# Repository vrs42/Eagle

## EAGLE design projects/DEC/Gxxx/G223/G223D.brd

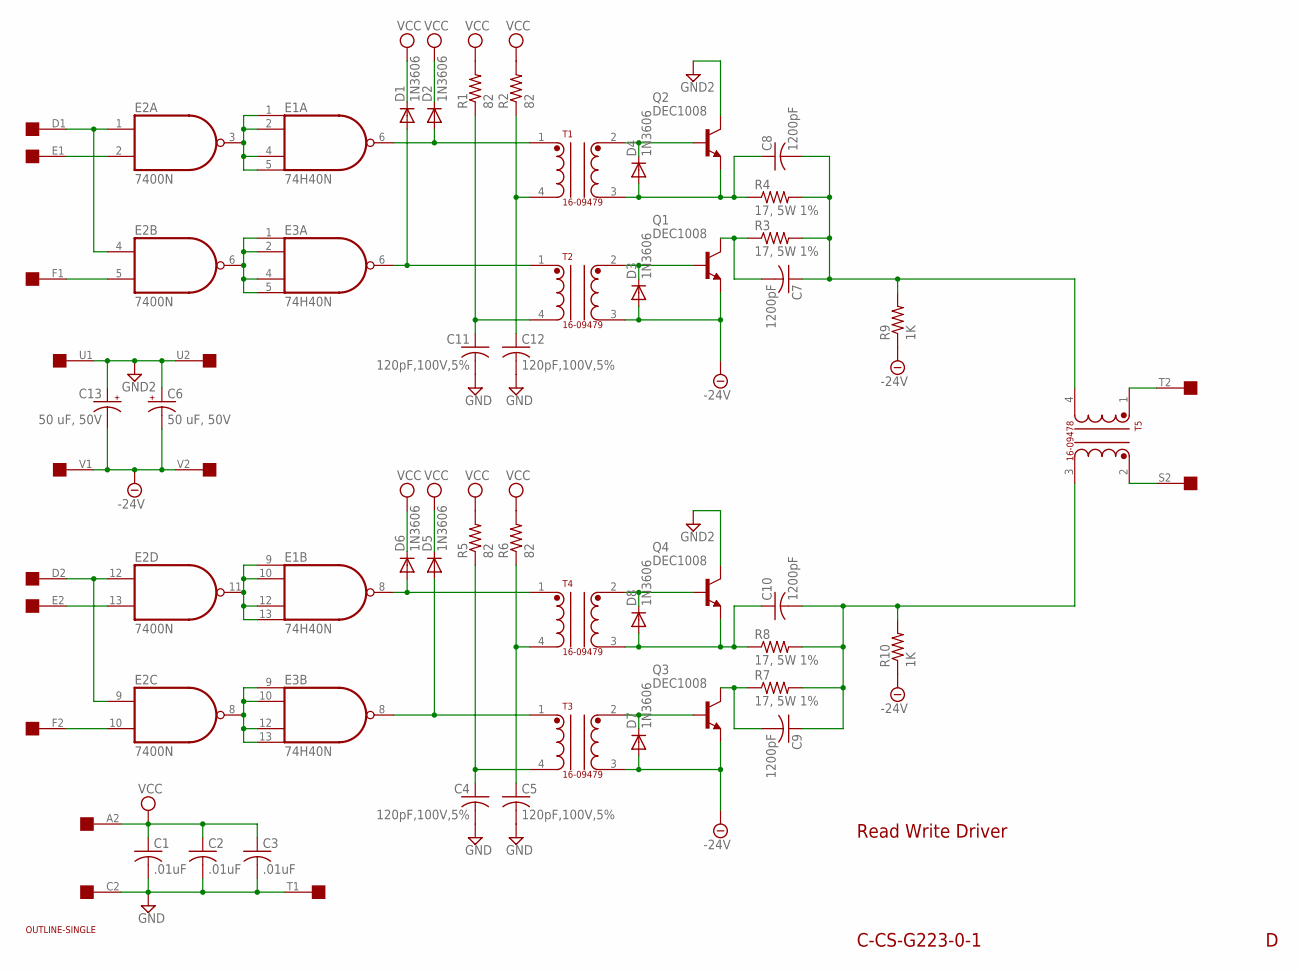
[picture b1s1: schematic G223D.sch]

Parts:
C1, C2, C3: .01uF; C050-025X075
C4, C5, C11, C12: 120pF,100V,5%; C075-032X103
C6, C13: 50 uF, 50V; E30-10
C7, C8, C9, C10: 1200pF; C075-032X103
D1, D2, D3, D4, D5, D6, D7, D8: 1N3606; DO35-10
E1, E3: 74H40N; DIL14
E2: 7400N; DIL14
EDGE1: EDGE-2CONNECTOR; EDGE-CON2
Q1, Q2, Q3, Q4: DEC1008; TO5
R1, R2, R5, R6: 82; 0207/10
R3, R4, R7, R8: 17, 5W 1%; VTA52
R9, R10: 1K; 0207/10
T1, T2, T3, T4: 16-09479; TRANSFORMER-SIL4
T5: 16-09478; TRANSFORMER-SIL4
U$1: OUTLINE-SINGLE; SINGLE

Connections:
-24V: C6.-, C13.-, D3.A, D7.A, EDGE1.V1, EDGE1.V2, Q1.1 (E), Q3.1 (E), R9.1, R10.1, T2.3, T3.3
GND: C1.2, C2.2, C3.2, C4.2, C5.2, C11.2, C12.2, E1.7 (GND), E2.7 (GND), E3.7 (GND), EDGE1.C2, EDGE1.T1
GND2: C6.+, C13.+, EDGE1.U1, EDGE1.U2, Q2.3 (C), Q4.3 (C)
unnamed: E1.1 (I0), E1.2 (I1), E1.4 (I2), E1.5 (I3), E2.3 (O)
unnamed: E2.1 (I0), E2.4 (I0), EDGE1.D1
unnamed: E2.2 (I1), EDGE1.E1
unnamed: E1.9 (I0), E1.10 (I1), E1.12 (I2), E1.13 (I3), E2.11 (O)
unnamed: E2.6 (O), E3.1 (I0), E3.2 (I1), E3.4 (I2), E3.5 (I3)
unnamed: E2.8 (O), E3.9 (I0), E3.10 (I1), E3.12 (I2), E3.13 (I3)
unnamed: E2.5 (I1), EDGE1.F1
unnamed: D2.A, E1.6 (O), T1.1
unnamed: D1.A, E3.6 (O), T2.1
unnamed: D6.A, E1.8 (O), T4.1
unnamed: D5.A, E3.8 (O), T3.1
unnamed: E2.9 (I0), E2.12 (I0), EDGE1.D2
unnamed: E2.13 (I1), EDGE1.E2
unnamed: E2.10 (I1), EDGE1.F2
unnamed: EDGE1.S2, T5.2
unnamed: EDGE1.T2, T5.1
unnamed: C7.1, C8.2, R3.2, R4.2, R9.2, T5.4
unnamed: C8.1, D4.A, Q2.1 (E), R4.1, T1.3
unnamed: C7.2, Q1.3 (C), R3.1
unnamed: C9.1, C10.2, R7.2, R8.2, R10.2, T5.3
unnamed: D7.C, Q3.2 (B), T3.2
unnamed: C9.2, Q3.3 (C), R7.1
unnamed: C10.1, D8.A, Q4.1 (E), R8.1, T4.3
unnamed: C11.1, R1.1, T2.4
unnamed: C12.1, R2.1, T1.4
unnamed: C5.1, R6.1, T4.4
unnamed: C4.1, R5.1, T3.4
unnamed: D3.C, Q1.2 (B), T2.2
unnamed: D4.C, Q2.2 (B), T1.2
unnamed: D8.C, Q4.2 (B), T4.2
VCC: C1.1, C2.1, C3.1, D1.C, D2.C, D5.C, D6.C, E1.14 (VCC), E2.14 (VCC), E3.14 (VCC), EDGE1.A2, R1.2, R2.2, R5.2, R6.2

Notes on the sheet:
Read Write Driver
C-CS-G223-0-1

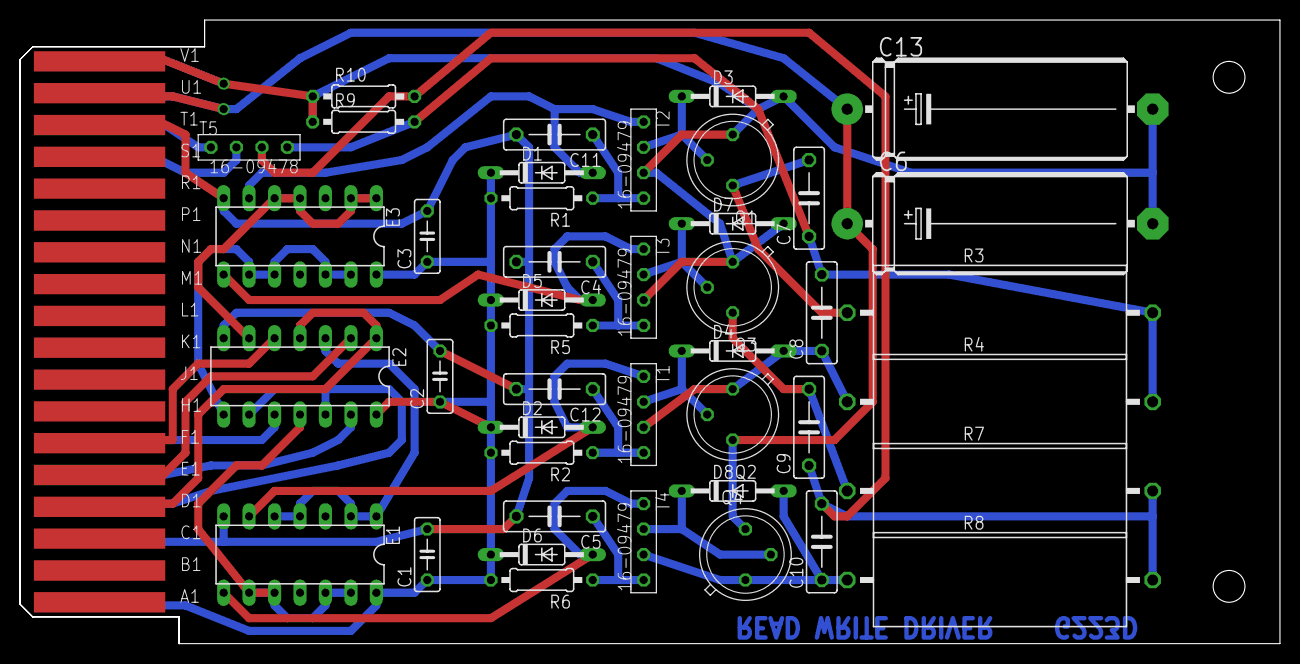
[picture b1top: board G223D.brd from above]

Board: 2 copper layers, 125.7 x 62.2 mm, 45 parts (0 on the bottom side), 34 nets.

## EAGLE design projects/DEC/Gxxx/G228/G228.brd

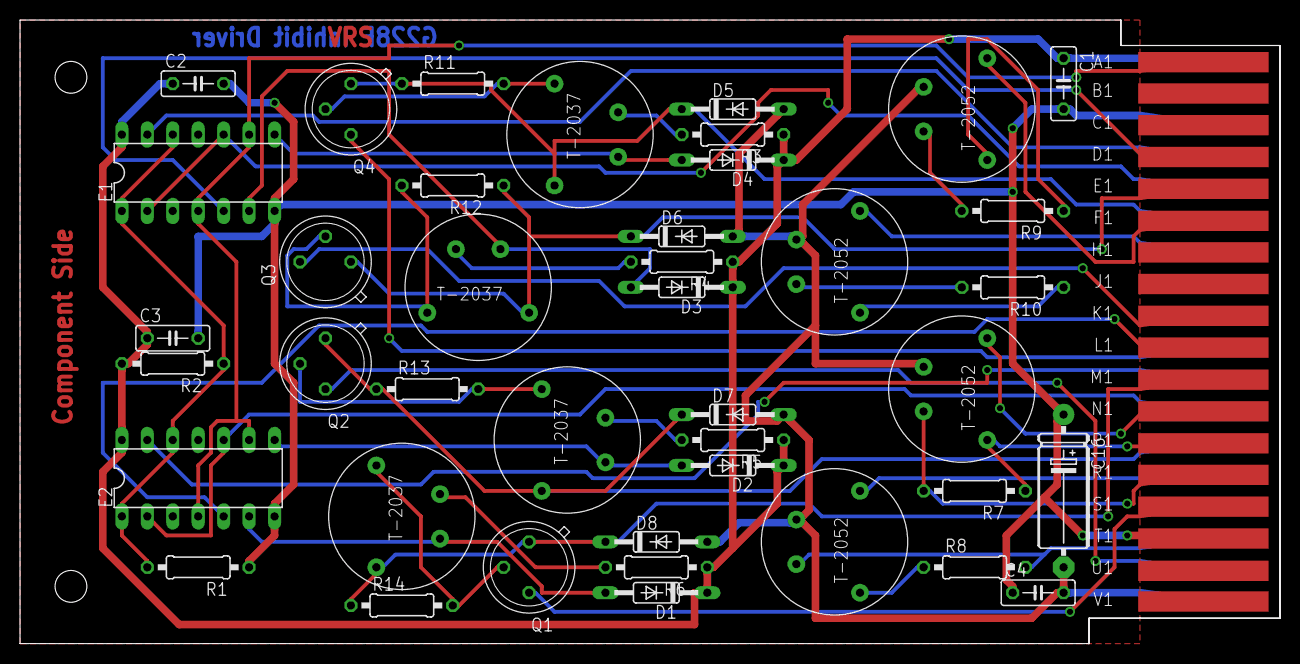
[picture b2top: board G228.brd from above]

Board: 2 copper layers, 125.7 x 62.2 mm, 43 parts (0 on the bottom side), 43 nets.

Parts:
C1, C2, C3, C4: .01uf; C050-025X075
C16: 20uf 50V; E15-5
D1, D2, D3, D4: 1N3606; DO35-10
D5, D6, D7, D8: 1N3653; DO35-10
E1, E2: 7440N; DIL14
Q1, Q2, Q3, Q4: TO39
R1: 750; 0207/10
R2, R3, R4, R5, R6: 330; 0207/10
R7, R8, R9, R10: 270; 0207/10
R11, R12, R13, R14: 470; 0207/10
T1, T2, T3, T4: T-2037; TRANSFORMER
T5, T6, T7, T8: T-2052; TRANSFORMER
U$1: EDGE-CON2
U$2: OUTLINE-SINGLE-R; SINGLE-R

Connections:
-24V: C4.2, C16.-, D5.A, D6.A, D7.A, D8.A, T5.4, T6.4, T7.4, T8.4, U$1.V2
A1: E1.4, E1.9, E2.4, E2.9, U$1.A1
D1: E1.5, U$1.D1
D2: E1.13, U$1.D2
E1: D6.C, Q3.1, R12.1, T3.2, U$1.E1
E2: E1.2, E1.10, U$1.E2
F1: T7.2, U$1.F1
F2: D5.C, Q4.1, R11.1, T4.2, U$1.F2
GND: C1.2, C2.2, C3.2, C4.1, C16.+, E1.7, E2.7, R1.1, U$1.C2, U$1.T1
H1: R9.1, T7.7
H2: T8.2, U$1.H2
J1: R9.2, T7.5
J2: R10.1, T8.7
K1: Q3.3, U$1.K1
K2: R10.2, T8.5
L1: E2.5, U$1.L1
L2: Q4.3, U$1.L2
M1: D8.C, Q1.1, R14.1, T1.2, U$1.M1
M2: E2.13, U$1.M2
N1: T5.2, U$1.N1
N2: E2.2, E2.10, U$1.N2
unnamed: E1.1, E1.12, E2.1, E2.12, R1.2, R2.1
unnamed: D1.A, E2.6, T1.4
unnamed: D2.A, E2.8, T2.4
unnamed: D3.A, E1.6, T3.4
unnamed: D4.A, E1.8, T4.4
unnamed: R6.2, T1.5
unnamed: R5.2, T2.5
unnamed: R4.2, T3.5
unnamed: R3.2, T4.5
unnamed: Q4.2, R11.2, T4.7
unnamed: Q3.2, R12.2, T3.7
unnamed: Q2.2, R13.2, T2.7
unnamed: Q1.2, R14.2, T1.7
P1: R7.1, T5.7, U$1.P1
P2: D7.C, Q2.1, R13.1, T2.2, U$1.P2
R1: R7.2, T5.5, U$1.R1
R2: T6.2, U$1.R2
S1: Q1.3, U$1.S1
S2: R8.1, T6.7
T2: R8.2, T6.5, U$1.T2
U2: Q2.3, U$1.U2
VCC: C1.1, C2.1, C3.1, D1.C, D2.C, D3.C, D4.C, E1.14, E2.14, R2.2, R3.1, R4.1, R5.1, R6.1, U$1.A2

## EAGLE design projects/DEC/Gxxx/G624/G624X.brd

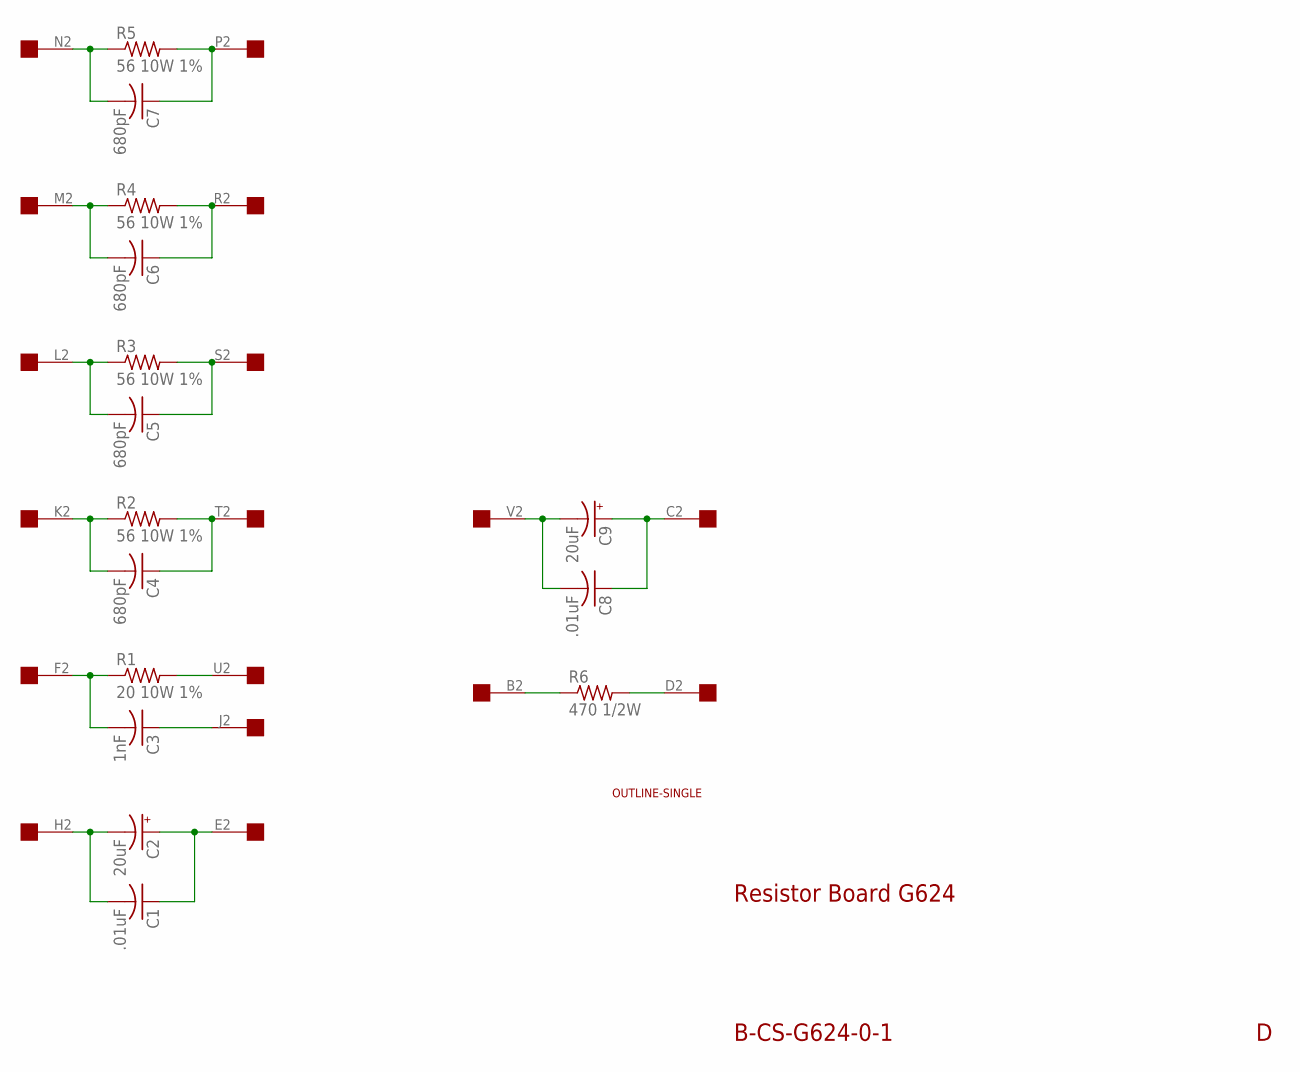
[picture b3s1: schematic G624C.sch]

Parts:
C1, C8: .01uF; C050-025X075
C2, C9: 20uF; E28-8
C3: 1nF; C050-025X075
C4, C5: 680pF; C150-054X183
C6, C7: 680pF; C050-025X075
R1: 20 10W 1%; 0944/51
R2, R3, R4, R5: 56 10W 1%; 0944/51
R6: 470 1/2W; 0411/15
U$1: EDGE-1; EDGE-CON1
U$2: OUTLINE-SINGLE; SINGLE

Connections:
unnamed: C3.2, R1.1, U$1.F2
unnamed: R1.2, U$1.U2
unnamed: C8.2, C9.-, U$1.V2
unnamed: C8.1, C9.+, U$1.C2
unnamed: C7.2, R5.1, U$1.N2
unnamed: C7.1, R5.2, U$1.P2
unnamed: C4.2, R2.1, U$1.K2
unnamed: C4.1, R2.2, U$1.T2
unnamed: C5.1, R3.2, U$1.S2
unnamed: C5.2, R3.1, U$1.L2
unnamed: C6.2, R4.1, U$1.M2
unnamed: C6.1, R4.2, U$1.R2
unnamed: C1.2, C2.-, U$1.H2
unnamed: C1.1, C2.+, U$1.E2
unnamed: R6.1, U$1.B2
unnamed: R6.2, U$1.D2
unnamed: C3.1, U$1.J2

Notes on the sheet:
Resistor Board G624
B-CS-G624-0-1

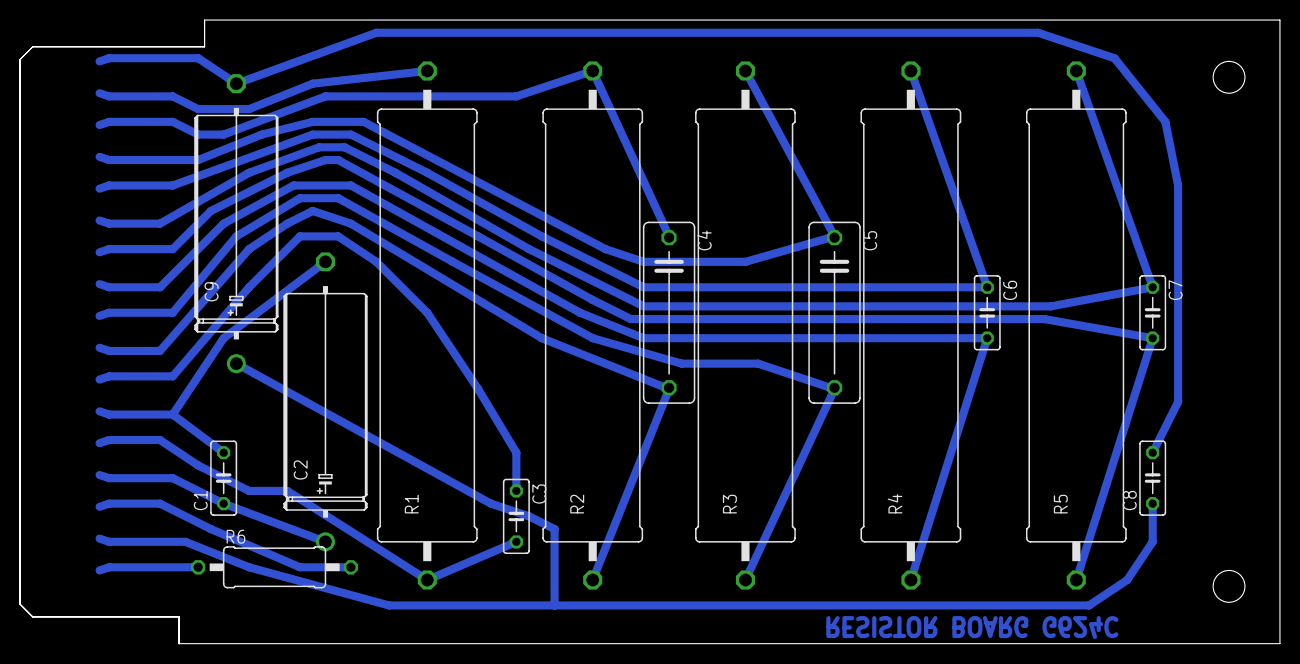
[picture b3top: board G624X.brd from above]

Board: 2 copper layers, 125.7 x 62.2 mm, 17 parts (0 on the bottom side), 17 nets.

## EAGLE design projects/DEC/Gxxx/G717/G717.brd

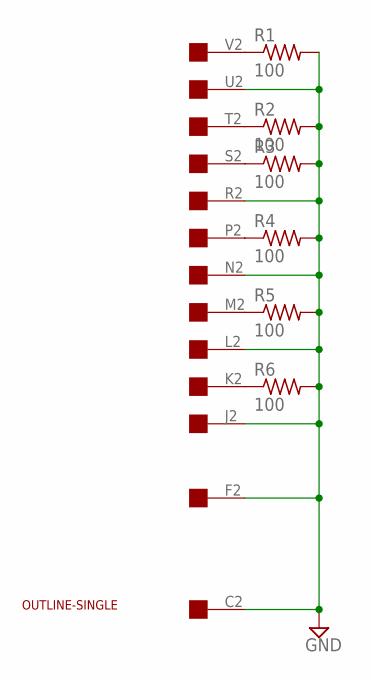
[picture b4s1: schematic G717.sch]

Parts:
R1, R2, R3, R4, R5, R6: 100; 0207/10
U$1: OUTLINE-SINGLE; SINGLE
U$3: EDGE-1; EDGE-CON1

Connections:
GND: R1.2, R2.2, R3.2, R4.2, R5.2, R6.2, U$3.C2, U$3.F2, U$3.J2, U$3.L2, U$3.N2, U$3.R2, U$3.U2
unnamed: R1.1, U$3.V2
unnamed: R2.1, U$3.T2
unnamed: R3.1, U$3.S2
unnamed: R4.1, U$3.P2
unnamed: R5.1, U$3.M2
unnamed: R6.1, U$3.K2

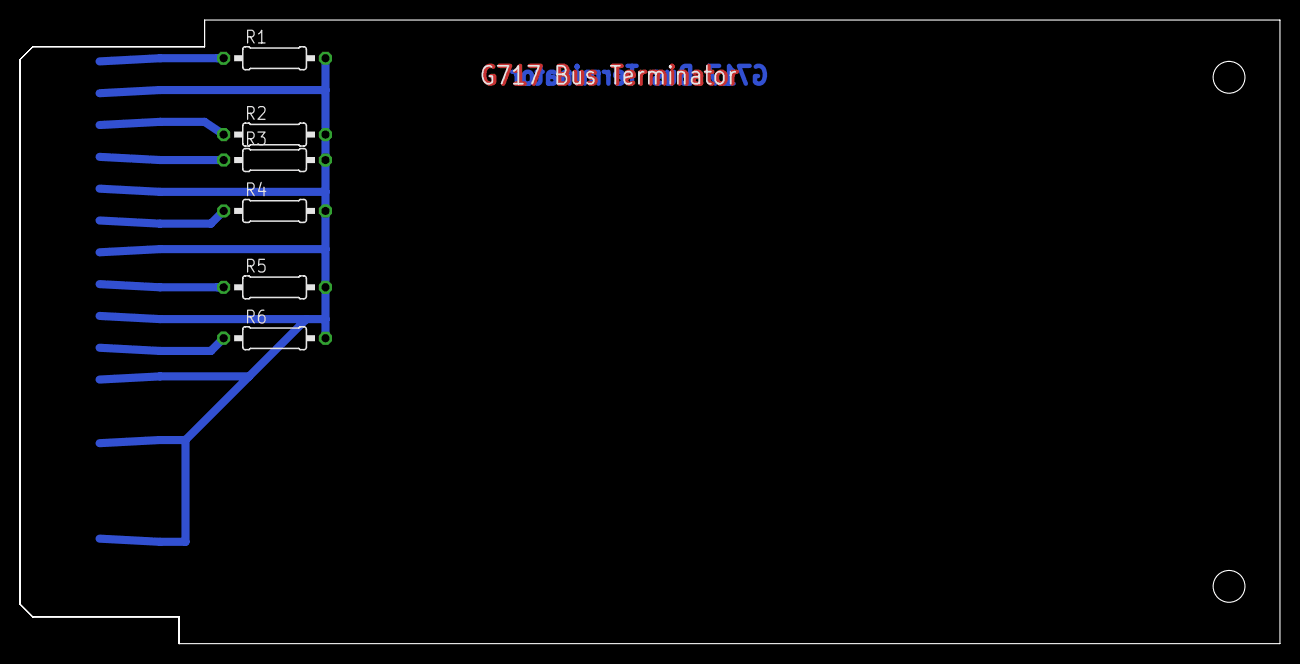
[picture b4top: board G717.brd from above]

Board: 2 copper layers, 125.7 x 62.2 mm, 8 parts (0 on the bottom side), 7 nets.

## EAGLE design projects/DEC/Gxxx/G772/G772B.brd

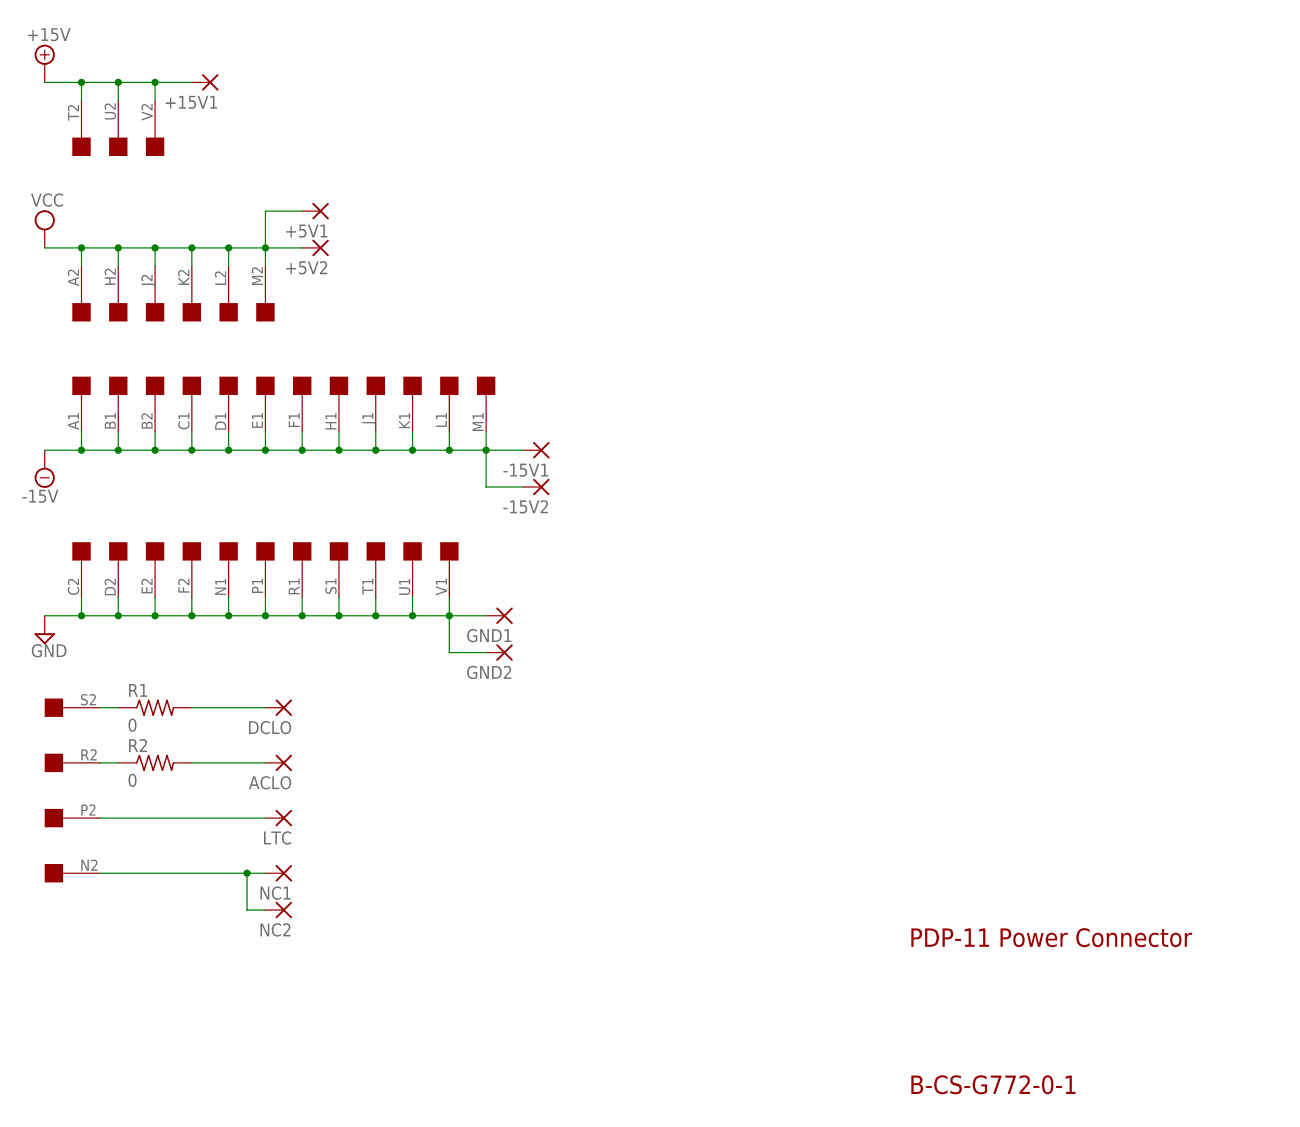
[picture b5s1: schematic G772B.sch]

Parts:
+5V1, +5V2, +15V1: 2,54/1,0
-15V1, -15V2: 2,54/1,0
ACLO: 2,54/1,0
DCLO: 2,54/1,0
GND1, GND2: 2,54/1,0
LTC: 2,54/1,0
NC1, NC2: 2,54/1,0
R1, R2: 0; 0207/10
U$1: SINGLE; EDGE-CON2

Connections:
+15V: +15V1.1, U$1.T2, U$1.U2, U$1.V2
-15V: -15V1.1, -15V2.1, U$1.A1, U$1.B1, U$1.B2, U$1.C1, U$1.D1, U$1.E1, U$1.F1, U$1.H1, U$1.J1, U$1.K1, U$1.L1, U$1.M1
ACLO: ACLO.1, R2.2
DCLO: DCLO.1, R1.2
GND: GND1.1, GND2.1, U$1.C2, U$1.D2, U$1.E2, U$1.F2, U$1.N1, U$1.P1, U$1.R1, U$1.S1, U$1.T1, U$1.U1, U$1.V1
LTC: LTC.1, U$1.P2
unnamed: R2.1, U$1.R2
unnamed: R1.1, U$1.S2
NC: NC1.1, NC2.1, U$1.N2
VCC: +5V1.1, +5V2.1, U$1.A2, U$1.H2, U$1.J2, U$1.K2, U$1.L2, U$1.M2

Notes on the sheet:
PDP-11 Power Connector
B-CS-G772-0-1

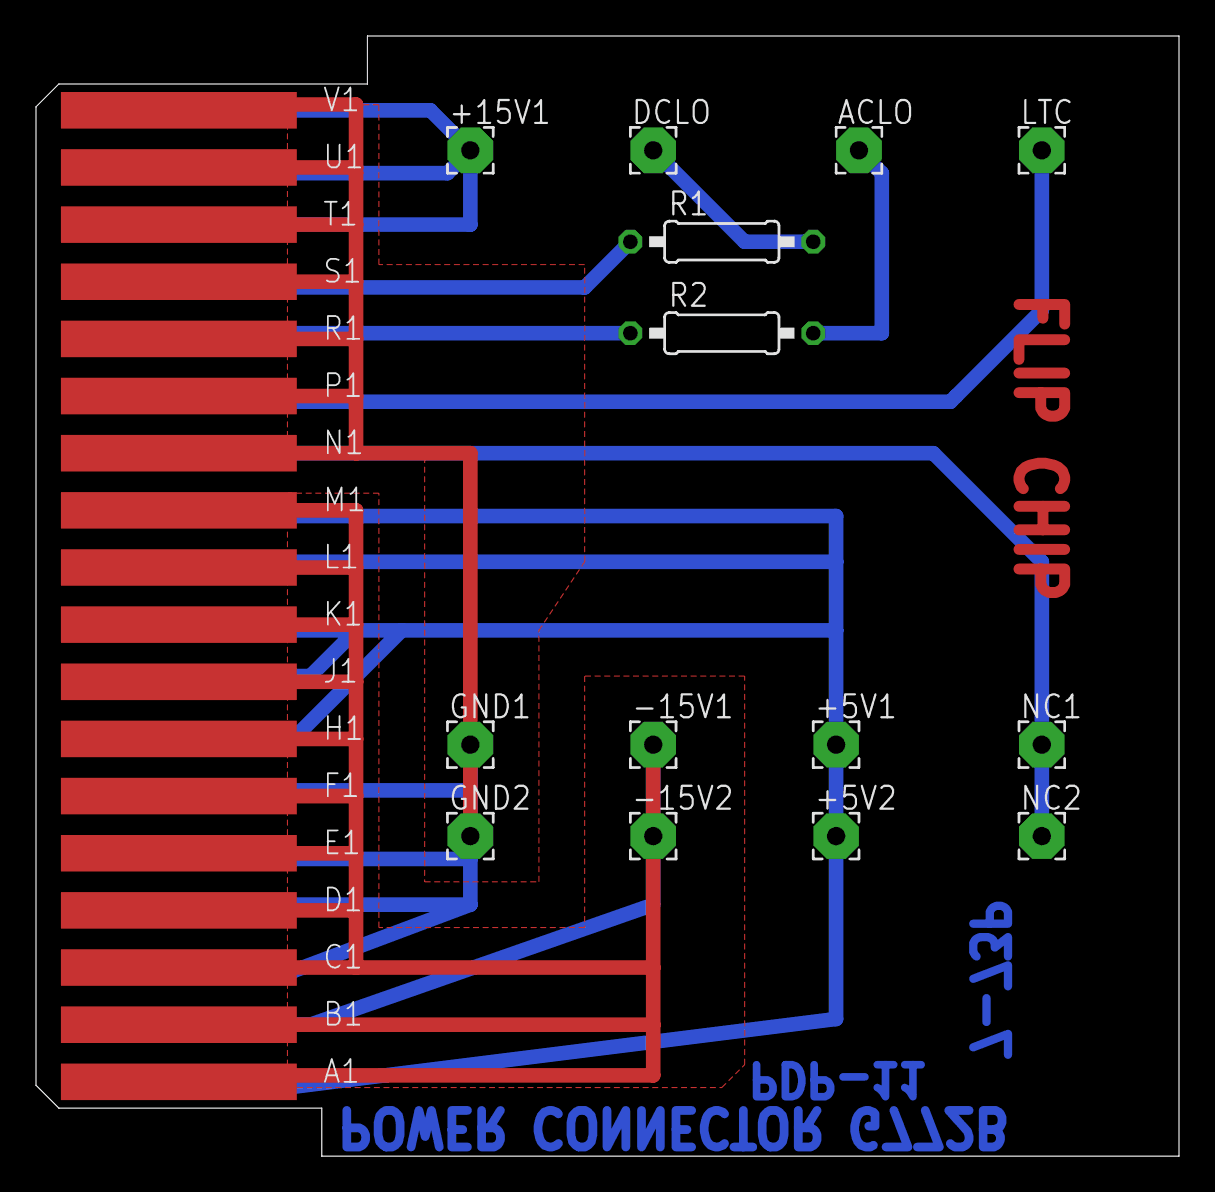
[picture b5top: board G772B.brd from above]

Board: 2 copper layers, 63.5 x 62.2 mm, 15 parts (0 on the bottom side), 10 nets.
